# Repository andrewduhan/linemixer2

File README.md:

linemixer2
=================

Simple active line mixer with input buffers.  
All through-hole components. 
Uses OPA2134 for buffers and summing.

Board measures 98.25mm x 59mm

Front and back panels measure 98.25mm x 19mm

The whole thing measures 98mm x 98.25mm

## NOTE: Schematic and board are untested!

## BOM:
* Jacks are Switchcraft 35RAPC4BH3  
* Channel pots are Bourns PTD902-2020K-A103
* Master (switched) pot is Bourns PTR902-2020K-A103
* DC Barrel jack is a standard CUI PJ-202A
* All capacitors are 6.30mm diameter, 2.5mm lead spacing.
* All resistors are the little 3.30mm guys

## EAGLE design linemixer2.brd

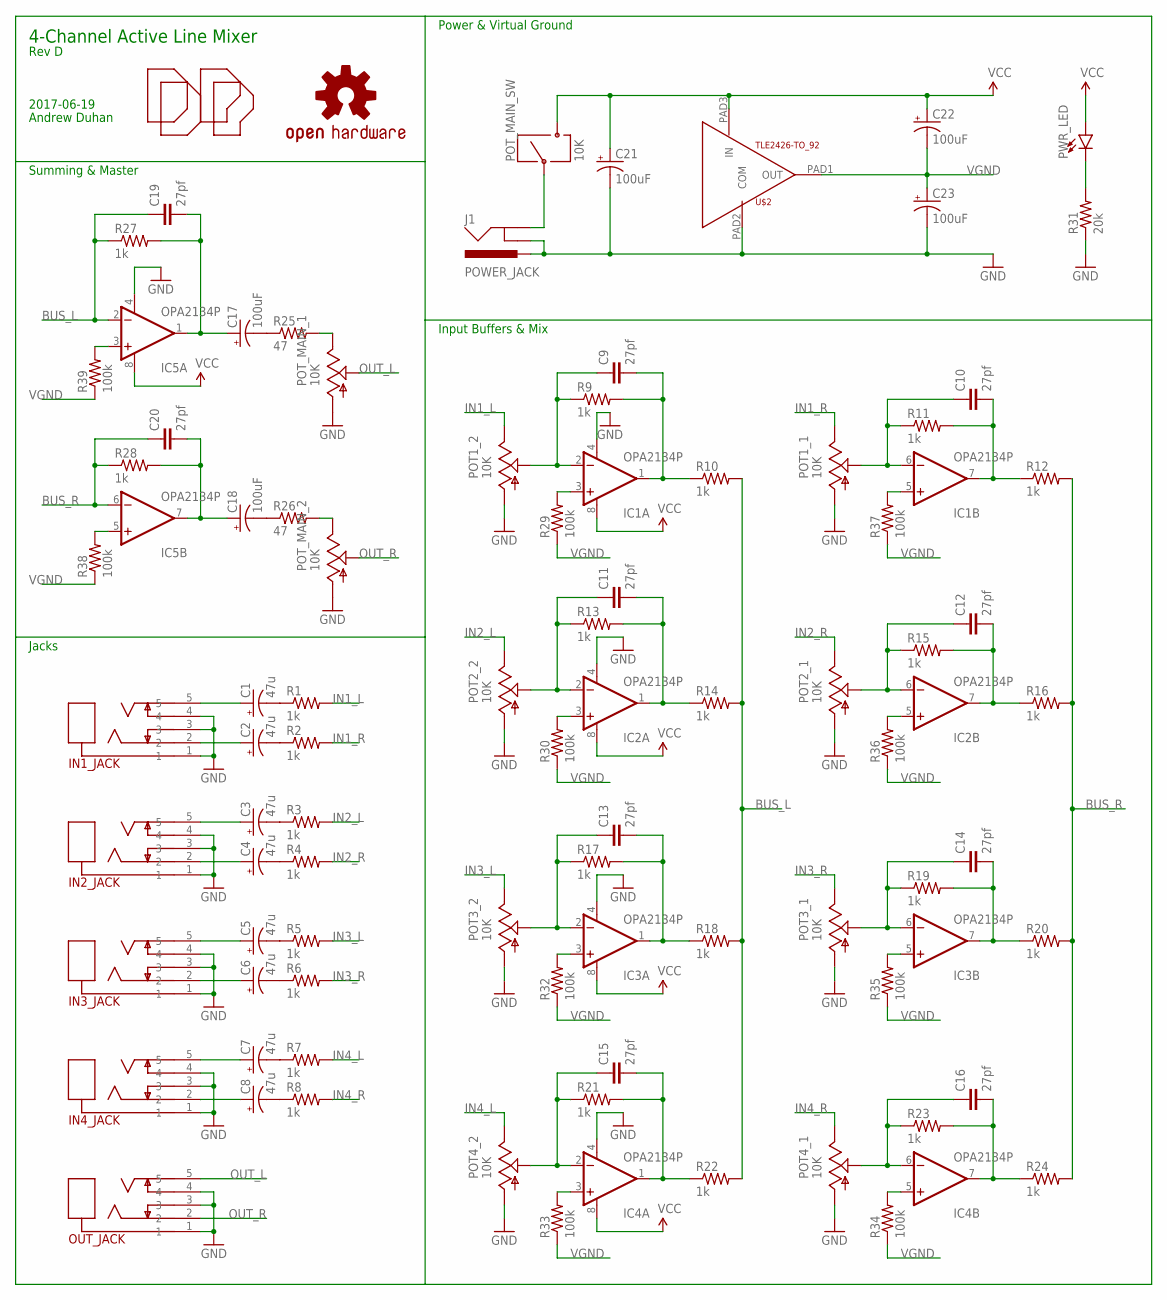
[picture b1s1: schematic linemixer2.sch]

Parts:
C1, C2, C3, C4, C5, C6, C7, C8: 47u; CPOL-RADIAL-2.5MM-6.5MM
C9, C10, C11, C12, C13, C14, C15, C16, C19, C20: 27pf; CAP-PTH-SMALL
C17, C18, C21, C22, C23: 100uF; CPOL-RADIAL-2.5MM-6.5MM
IC1, IC2, IC3, IC4, IC5: OPA2134P; DIL08
IN1_JACK, IN2_JACK, IN3_JACK, IN4_JACK: JACK_STEREO_SWCUI-SJ1-351X; AUDIO_JACK-CUI-SJ1-351X
J1: POWER_JACK; POWER_JACK_PTH
LOGO1: OSHW-LOGOS; OSHW-LOGO-S
OUT_JACK: JACK_STEREO_SWCUI-SJ1-351X; AUDIO_JACK-CUI-SJ1-351X
POT1_, POT2_, POT3_, POT4_: 10K; BOURNS_PTD902
POT_MAIN_: 10K; BOURNS_PTR902
PWR_LED: LED3MM; LED_3MM
R1, R2, R3, R4, R5, R6, R7, R8, R9, R10, R11, R12, R13, R14, R15, R16, R17, R18, R19, R20, R21, R22, R23, R24, R27, R28: 1k; 0204/5
R25, R26: 47; 0204/5
R29, R30, R32, R33, R34, R35, R36, R37, R38, R39: 100k; 0204/5
R31: 20k; 0204/5
U$1, U$3: DP_LOGO
U$2: TLE2426-TO_92; TO-92

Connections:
BUS_L: C19.1, IC5.2 (-IN), R10.2, R14.2, R18.2, R22.2, R27.1
BUS_R: C20.1, IC5.6 (-IN), R12.2, R16.2, R20.2, R24.2, R28.1
GND: C21.2 (-), C23.2 (-), IC1.4 (V-), IC2.4 (V-), IC3.4 (V-), IC4.4 (V-), IC5.4 (V-), IN1_JACK.1, IN1_JACK.3, IN1_JACK.4, IN2_JACK.1, IN2_JACK.3, IN2_JACK.4, IN3_JACK.1, IN3_JACK.3, IN3_JACK.4, IN4_JACK.1, IN4_JACK.3, IN4_JACK.4, J1.GNDBREAK, J1.PWR, OUT_JACK.1, OUT_JACK.3, OUT_JACK.4, POT1_.R1-A (A), POT1_.R2-A (A), POT2_.R1-A (A), POT2_.R2-A (A), POT3_.R1-A (A), POT3_.R2-A (A), POT4_.R1-A (A), POT4_.R2-A (A), POT_MAIN_.R1-A (A), POT_MAIN_.R2-A (A), R31.1, U$2.PAD2 (COM)
IN1_L: POT1_.R2-B (B), R1.2
IN1_R: POT1_.R1-B (B), R2.2
IN2_L: POT2_.R2-B (B), R3.2
IN2_R: POT2_.R1-B (B), R4.2
IN3_L: POT3_.R2-B (B), R5.2
IN3_R: POT3_.R1-B (B), R6.2
IN4_L: POT4_.R2-B (B), R7.2
IN4_R: POT4_.R1-B (B), R8.2
unnamed: C1.1 (+), IN1_JACK.5
unnamed: C2.1 (+), IN1_JACK.2
unnamed: C3.1 (+), IN2_JACK.5
unnamed: C4.1 (+), IN2_JACK.2
unnamed: C5.1 (+), IN3_JACK.5
unnamed: C6.1 (+), IN3_JACK.2
unnamed: C7.1 (+), IN4_JACK.5
unnamed: C8.1 (+), IN4_JACK.2
unnamed: C1.2 (-), R1.1
unnamed: C2.2 (-), R2.1
unnamed: C3.2 (-), R3.1
unnamed: C4.2 (-), R4.1
unnamed: C5.2 (-), R5.1
unnamed: C6.2 (-), R6.1
unnamed: C7.2 (-), R7.1
unnamed: C8.2 (-), R8.1
unnamed: C9.2, IC1.1 (OUT), R9.2, R10.1
unnamed: C11.2, IC2.1 (OUT), R13.2, R14.1
unnamed: IC1.3 (+IN), R29.2
unnamed: IC5.3 (+IN), R39.2
unnamed: C10.2, IC1.7 (OUT), R11.2, R12.1
unnamed: C17.1 (+), C19.2, IC5.1 (OUT), R27.2
unnamed: C18.1 (+), C20.2, IC5.7 (OUT), R28.2
unnamed: IC5.5 (+IN), R38.2
unnamed: C12.2, IC2.7 (OUT), R15.2, R16.1
unnamed: C13.2, IC3.1 (OUT), R17.2, R18.1
unnamed: C14.2, IC3.7 (OUT), R19.2, R20.1
unnamed: IC2.3 (+IN), R30.2
unnamed: C15.2, IC4.1 (OUT), R21.2, R22.1
unnamed: C16.2, IC4.7 (OUT), R23.2, R24.1
unnamed: IC3.3 (+IN), R32.2
unnamed: C17.2 (-), R25.1
unnamed: C18.2 (-), R26.1
unnamed: POT_MAIN_.R1-B (B), R25.2
unnamed: POT_MAIN_.R2-B (B), R26.2
unnamed: C9.1, IC1.2 (-IN), POT1_.R2-W (W), R9.1
unnamed: PWR_LED.K (C), R31.2
unnamed: J1.GND, POT_MAIN_.P$2 (2)
unnamed: IC4.3 (+IN), R33.2
unnamed: IC4.5 (+IN), R34.2
unnamed: IC3.5 (+IN), R35.2
unnamed: C13.1, IC3.2 (-IN), POT3_.R2-W (W), R17.1
unnamed: C11.1, IC2.2 (-IN), POT2_.R2-W (W), R13.1
unnamed: C15.1, IC4.2 (-IN), POT4_.R2-W (W), R21.1
unnamed: IC2.5 (+IN), R36.2
unnamed: IC1.5 (+IN), R37.2
unnamed: C10.1, IC1.6 (-IN), POT1_.R1-W (W), R11.1
unnamed: C12.1, IC2.6 (-IN), POT2_.R1-W (W), R15.1
unnamed: C14.1, IC3.6 (-IN), POT3_.R1-W (W), R19.1
unnamed: C16.1, IC4.6 (-IN), POT4_.R1-W (W), R23.1
OUT_L: OUT_JACK.5, POT_MAIN_.R1-W (W)
OUT_R: OUT_JACK.2, POT_MAIN_.R2-W (W)
VCC: C21.1 (+), C22.1 (+), IC1.8 (V+), IC2.8 (V+), IC3.8 (V+), IC4.8 (V+), IC5.8 (V+), POT_MAIN_.P$1 (1), PWR_LED.A, U$2.PAD3 (IN)
VGND: C22.2 (-), C23.1 (+), R29.1, R30.1, R32.1, R33.1, R34.1, R35.1, R36.1, R37.1, R38.1, R39.1, U$2.PAD1 (OUT)

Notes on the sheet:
4-Channel Active Line Mixer
Andrew Duhan
Rev D
2017-06-19
Jacks
Summing & Master
Power & Virtual Ground
Input Buffers & Mix

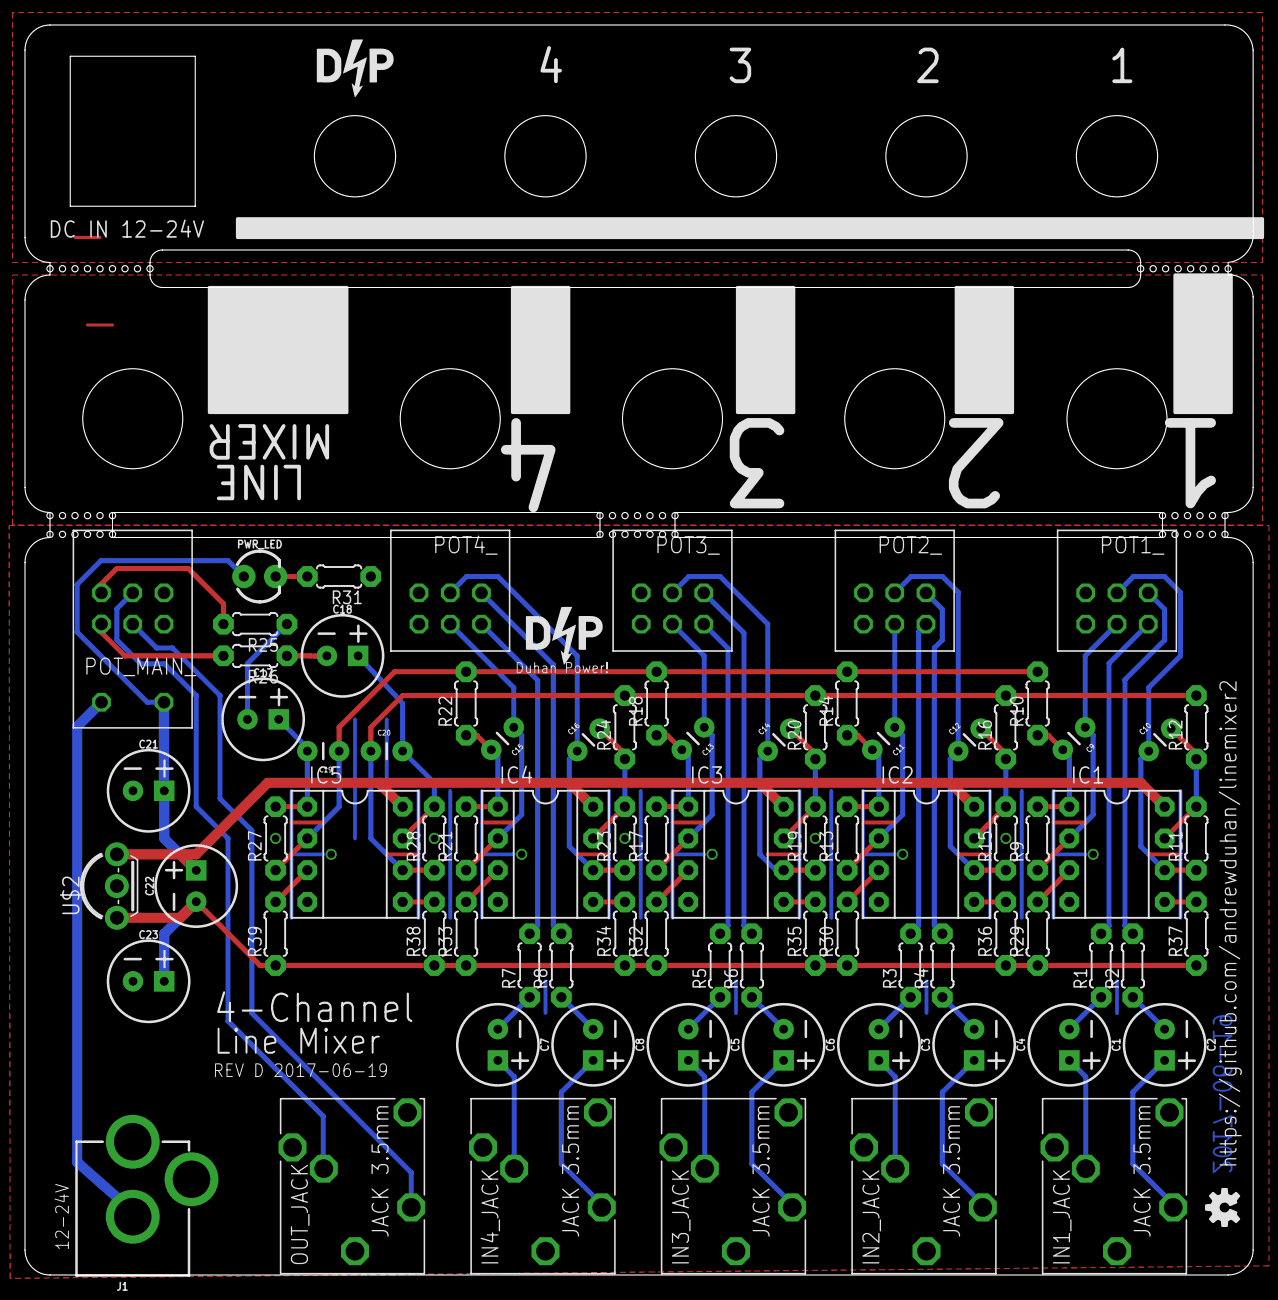
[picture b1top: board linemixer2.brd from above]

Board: 2 copper layers, 98.3 x 100.0 mm, 83 parts (0 on the bottom side), 65 nets.

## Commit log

2017-05-30 initial commit, Rev A. Untested.
2017-05-30 board image
2017-05-30 change resistors to 3mm and tweak
2017-06-12 rev b
2017-06-13 rev B tweaks and images
2017-06-13 update board dimensions
2017-06-19 rev c - add resistors to the vgnd on each opamp
2017-06-22 rev D
2017-06-22 readme: update board dimensions
2017-06-22 readme formatting

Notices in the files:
parts and their libraries:
SparkFun-Capacitors: Licensing: Creative Commons ShareAlike 4.0 International - https://creativecommons.org/licenses/by-sa/4.0
